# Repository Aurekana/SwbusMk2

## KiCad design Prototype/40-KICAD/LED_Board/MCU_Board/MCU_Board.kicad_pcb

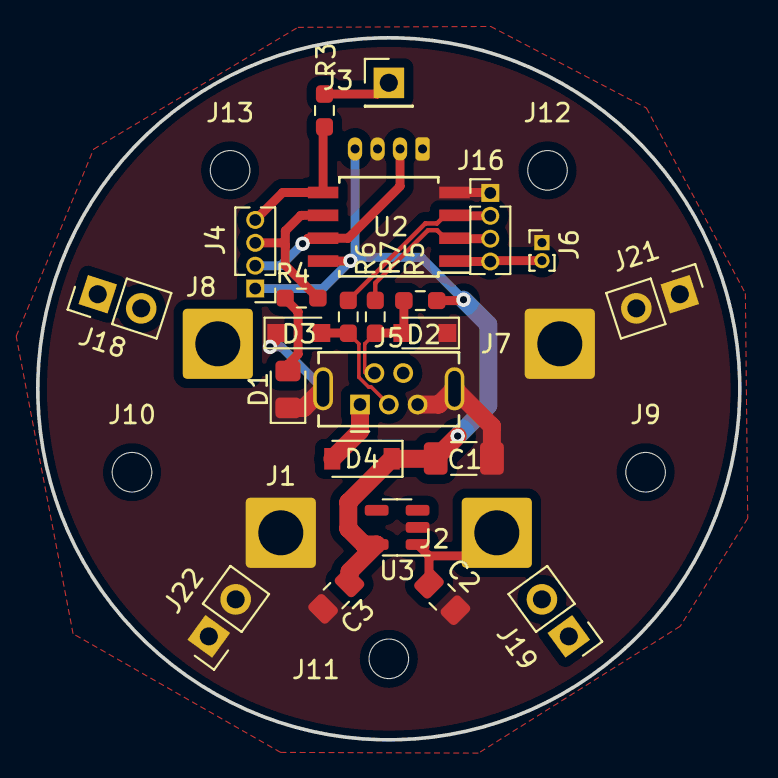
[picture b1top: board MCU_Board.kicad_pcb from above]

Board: 2 copper layers, 39.0 x 39.0 mm, 33 parts (1 on the bottom side), 14 nets.

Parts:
C1: 10uF; C_1206_3216Metric_Pad1.33x1.80mm_HandSolder
C2: 1uF; C_0805_2012Metric_Pad1.18x1.45mm_HandSolder
C3: 2.2uF; C_0805_2012Metric_Pad1.18x1.45mm_HandSolder
D1: LED; LED_0805_2012Metric_Pad1.15x1.40mm_HandSolder
D2, D3: 3.6V; D_SOD-323_HandSoldering
D4: D_Schottky; D_SOD-123
J1, J2, J7, J8: Conn_01x01; SolderWire-2sqmm_1x01_D2mm_OD3.9mm
J3: Conn_01x01; PinHeader_1x01_P2.54mm_Vertical
J4, J16: Conn_01x04; PinHeader_1x04_P1.27mm_Vertical
J5: USB_B_Micro; USB_Mini-B_Tensility_54-00023_Vertical
J6: Conn_01x02; PinHeader_1x02_P1.00mm_Vertical
J9, J10, J11, J12, J13: Conn_01x01; MountingHole_2.2mm_M2
J18, J19, J21, J22: Conn_01x02; PinHeader_1x02_P2.54mm_Vertical
J20: Conn_01x04; Molex_PicoBlade_53047-0410_1x04_P1.25mm_Vertical
R3: 500; R_0603_1608Metric_Pad0.98x0.95mm_HandSolder
R4: 470; R_0603_1608Metric_Pad0.98x0.95mm_HandSolder
R5: 1.5K; R_0603_1608Metric_Pad0.98x0.95mm_HandSolder
R6, R7: 68; R_0603_1608Metric_Pad0.98x0.95mm_HandSolder
U2: ATtiny85-20SU; SOIJ-8_5.3x5.3mm_P1.27mm
U3: MIC5219-5.0YM5; SOT-23-5

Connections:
+5V: C1.1, C3.1, D4.1 (K), J4.1, J20.4, R5.1, U2.8 (VCC), U3.5 (OUT)
+12V: C2.1, J2.1, J8.1, J18.1, J18.2, J19.1, J19.2, U3.1 (IN)
/D_N: D2.2 (A), J5.2 (D-), R5.2, R7.2
/D_P: D3.2 (A), J5.3 (D+), R6.2
B0: J4.4, R3.2, U2.5 (AREF/PB0)
B1: J4.3, R4.2, U2.6 (PB1)
B2: J4.2, J20.2, U2.7 (PB2)
GND: C1.2, C2.2, C3.2, D1.1 (K), D2.1 (K), D3.1 (K), J1.1, J5.5 (GND), J5.6 (Shield), J6.1, J7.1, J16.1, J20.1, J20.3, J21.1, J21.2, J22.1, J22.2, U2.4 (GND), U3.2 (GND)
unnamed: D1.2 (A), R4.1
unnamed: J3.1, R3.1
RESET: J6.2, J16.4, U2.1 (~RESET/PB5)
USB_N: J16.3, R7.1, U2.2 (XTAL1/PB3)
USB_P: J16.2, R6.1, U2.3 (XTAL2/PB4)
VBUS: D4.2 (A), J5.1 (VBUS)

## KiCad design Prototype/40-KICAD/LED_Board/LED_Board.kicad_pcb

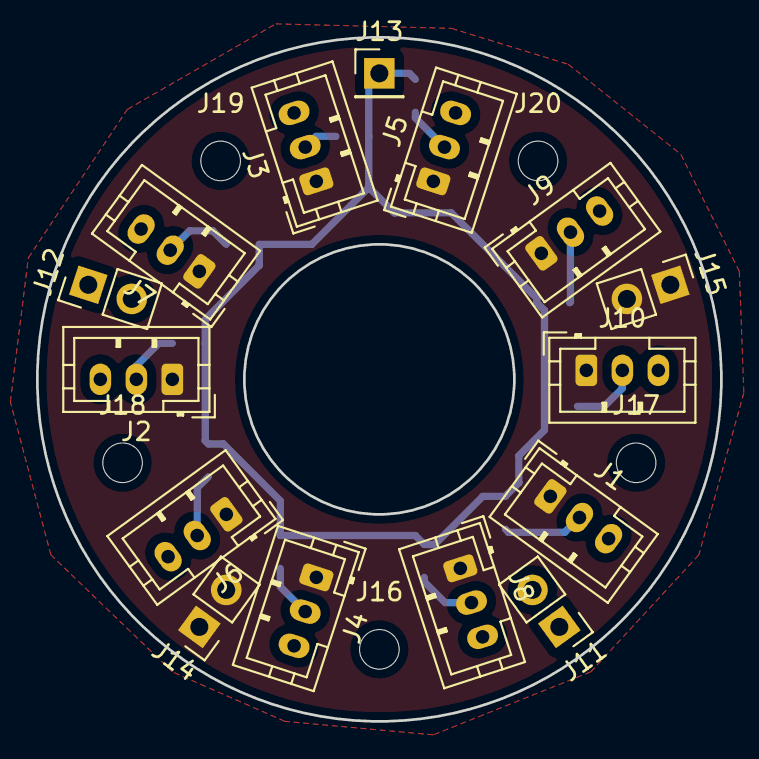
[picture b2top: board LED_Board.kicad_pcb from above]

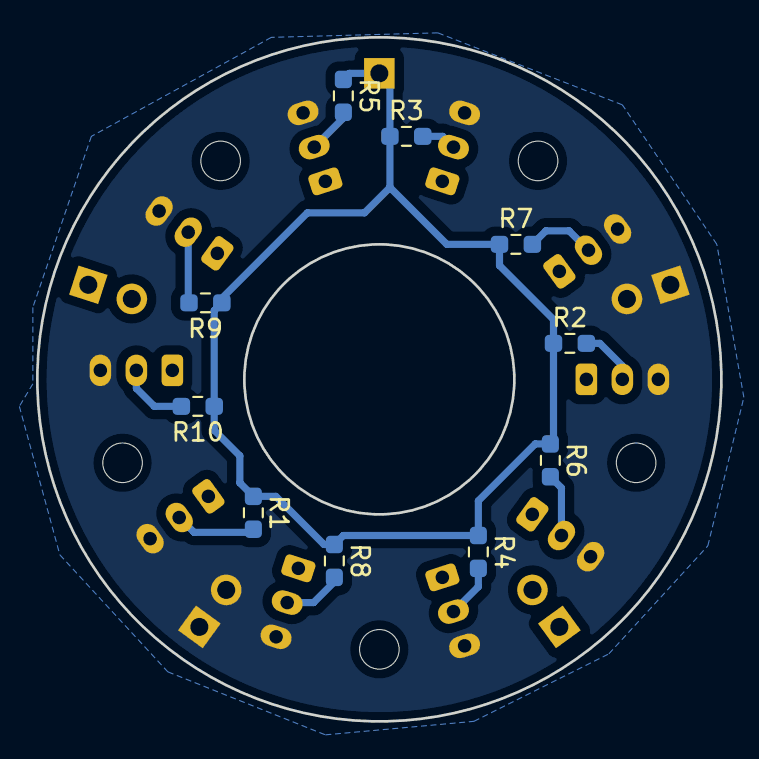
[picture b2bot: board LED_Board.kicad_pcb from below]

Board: 2 copper layers, 38.0 x 38.0 mm, 30 parts (10 on the bottom side), 13 nets.

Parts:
J1, J2, J3, J4, J5, J6, J7, J8, J9, J10: Conn_01x03; JST_PH_B3B-PH-K_1x03_P2.00mm_Vertical
J11, J12, J14, J15: Conn_01x02; PinHeader_1x02_P2.54mm_Vertical
J13: Conn_01x01; PinHeader_1x01_P2.54mm_Vertical
J16, J17, J18, J19, J20: Conn_01x01; MountingHole_2.2mm_M2
R1, R2, R3, R4, R5, R6, R7, R8, R9, R10: 500R; R_0603_1608Metric_Pad0.98x0.95mm_HandSolder

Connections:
+5V: J1.3, J2.3, J3.3, J4.3, J5.3, J6.3, J7.3, J8.3, J9.3, J10.3, J11.1, J11.2, J12.1, J12.2
GND: J1.1, J2.1, J3.1, J4.1, J5.1, J6.1, J7.1, J8.1, J9.1, J10.1, J14.1, J14.2, J15.1, J15.2
NEO: J13.1, R1.1, R2.1, R3.1, R4.1, R5.1, R6.1, R7.1, R8.1, R9.1, R10.1
unnamed: J1.2, R1.2
unnamed: J2.2, R2.2
unnamed: J3.2, R3.2
unnamed: J4.2, R4.2
unnamed: J5.2, R5.2
unnamed: J6.2, R6.2
unnamed: J7.2, R7.2
unnamed: J8.2, R8.2
unnamed: J9.2, R9.2
unnamed: J10.2, R10.2

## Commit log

2022-11-18 Update folder structure
2022-11-18 Add verified parts
2022-11-18 Parts added
2022-11-18 Updated Part Naming Scheme
2022-11-18 BOM added
2022-11-18 BOM updated
2022-12-19 Added STEP files
2022-12-19 Updated Assy
2022-12-24 Added Mainboard KiCAD
2022-12-24 Added KiCAD
2023-01-11 Updated Barrel Assy geometry
2023-01-11 Updated geometry
2023-01-25 Doc update
2023-01-26 Updated assembly docs
2023-01-26 Assembly Docs
2023-01-26 BOM update
2023-01-27 Arduino sketch
2023-01-27 Program update
2023-01-31 12V ws2815 compatibility
2023-01-31 Updated PCB
    Level shifter not required for ws2815 (5V logic)
2023-04-19 Updated stl files
2024-12-08 LED code update
2024-12-12 Added parts
